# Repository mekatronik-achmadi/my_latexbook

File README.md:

# Install LaTeX

## Contents
- [ArchLinux](#archlinux)
	+ [TeXLive](#texlive)
	+ [TeXStudio](#texstudio)
	+ [Visual Studio Code](#visual-studio-code)
	+ [Makefile](#makefile)
- [Windows](#windows)
	+ [TeXLive](#texlive-1)
	+ [TeXStudio](#texstudio-1)

## ArchLinux

Example install command for ArchLinux, Manjaro, or any other Arch-based GNU/Linux distributions OS.

### TeXLive

To install TeXLive package, you can use command:

```sh
sudo pacman -S texlive-most texlive-bin latex2html latex2rtf dblatex minted biber pdftk
```

It will download approximately 800MB and installation size about 2.5GB.

This should be reproducible in other GNU/Linux distributions like Ubuntu or Fedora.

### TeXStudio

For editor, you can choose TeXStudio and can be installed using command:

```sh
sudo pacman -S texstudio
```

Installation size approximately 500MB (including Qt5 toolkit)

**NOTE:** If you use **minted**, you should use **-shell-escape**.
 
 Go to menu *Options* -> *Configure TexStudio* -> *Commands* to add **-shell-escape** like this:.

### Visual Studio Code

You can also use general code editor like Visual Studio Code to write LaTeX document.

First install VSCodium from this AUR package: https://aur.archlinux.org/packages/vscodium-bin/

Then install **LaTeX-Workshop** extension from *View* -> *Extension*.

### Makefile

You can also use this **Makefile** to build PDF from LaTeX documents

```make
TEXCC=pdflatex
BIBCC=bibtex
TEXFLAGS=-shell-escape -synctex=1 -interaction=nonstopmode
TEXFILE=$(shell basename --suffix=.tex $$(ls -1 *.tex))

# '-' sign mean keep going even if the command fail
all:
	-$(TEXCC) $(TEXFLAGS) $(TEXFILE).tex
	-$(BIBCC) $(TEXFILE).aux
	-$(TEXCC) $(TEXFLAGS) $(TEXFILE).tex
	-$(TEXCC) $(TEXFLAGS) $(TEXFILE).tex # run twice to update ToC/BibTeX

clean:
	rm -f *.out *.bbl *.blg *.lof *.lot *.nav *.vrb
	rm -f *.log *.toc *.synctex.gz  *.pyg *.snm
	rm -f *.aux *Notes.bib
	rm -f *.pdf
	rm -rf ./_minted*
```

Save as Makefile in same directory of any LaTeX documents, then run command:

```sh
make all
```

and to clean up you can run commmand:

```sh
make clean
```

## Windows

Example install process for Windows OS.

### TeXLive

Here step to Download TeXLive package:
- Open Mirror CTAN: https://ctan.org/mirrors.
- Choose closest mirror. Then choose **TeX Live**.
- Choose **Images**. Click to download the ISO file.

For example, Indonesian users can use this ISO file URL:

http://repo.ugm.ac.id/ctan/systems/texlive/Images/texlive2022-20220321.iso

**NOTE:** The ISO file approximately 5GB.

After download the ISO, first mount the ISO file (for example here as **E:** drive)

Then open **CMD** to run these commands:

```sh
> E:
> install-tl-windows.bat --location "E:/"
```

**NOTE:** Leave the CMD Window open during installations process

When GUI installer shown up, choose *Advanced*

Here there some recommended adjustments:
- Check *Adjust searchpath*.
- Choose *All* for *File associations*.
- Uncheck *Install TeXWorks* since TeXStudio will be used here.

Next go to *Selections* and click *Customize*.

In *Language* part, click *None* and then check only *US and UK English*

Then Click *Apply* and *OK*. The installation size should be reduced.

Last, click *Install* and wait until finished.

### TexStudio

You can download the Windows binary from Github release page:

https://github.com/texstudio-org/texstudio/releases/

**NOTE:** If you use **minted**, you should use **-shell-escape**.
 
 Go to menu *Options* -> *Configure TexStudio* -> *Commands* to add **-shell-escape** like this:.

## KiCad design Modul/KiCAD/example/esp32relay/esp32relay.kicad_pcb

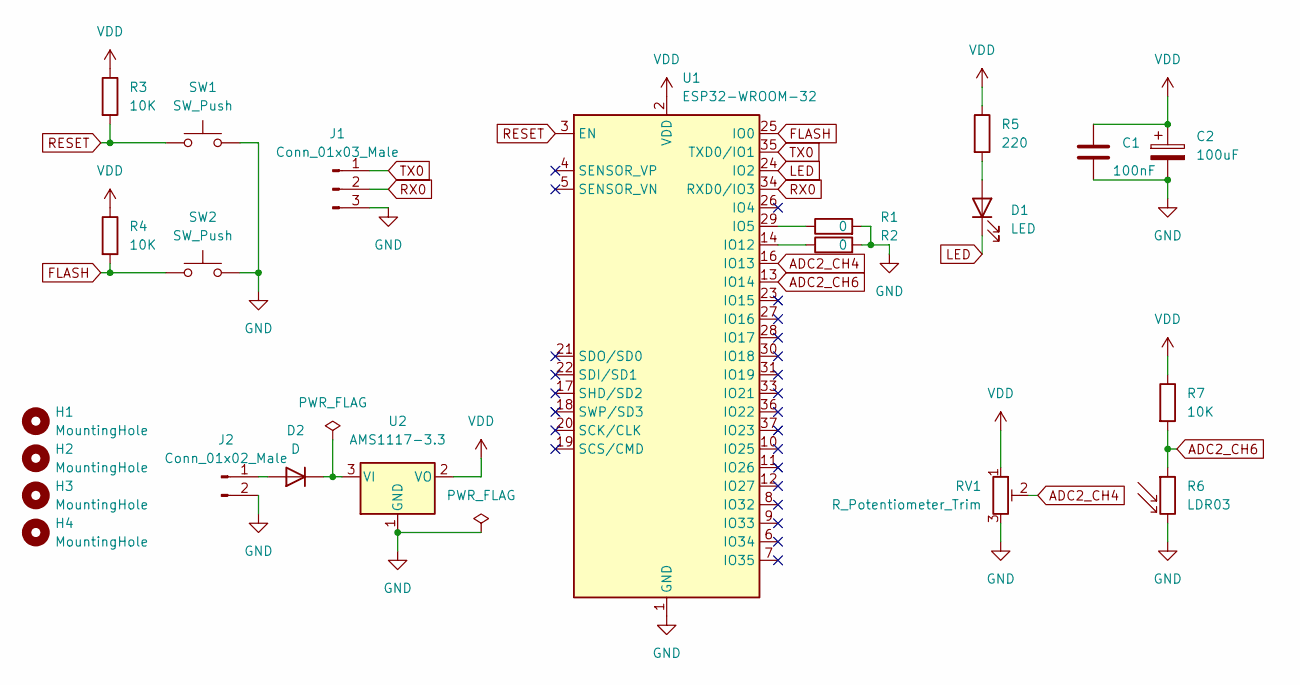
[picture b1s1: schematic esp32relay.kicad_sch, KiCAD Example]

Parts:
C1: 100nF; C_0805_2012Metric
C2: 100uF; C_0805_2012Metric
D1: LED; LED_0805_2012Metric
D2: D; D_SMA
H1, H2, H3, H4: MountingHole; MountingHole_2.5mm_Pad_Via
J1: Conn_01x03_Male; PinHeader_1x03_P2.54mm_Horizontal
J2: Conn_01x02_Male; Altech_AK300_1x02_P5.00mm_45-Degree
R1, R2: 0; R_0805_2012Metric
R3, R4, R7: 10K; R_0805_2012Metric
R5: 220; R_0805_2012Metric
R6: LDR03; R_LDR_10x8.5mm_P7.6mm_Vertical
RV1: R_Potentiometer_Trim; Potentiometer_Vishay_TS53YJ_Vertical
SW1, SW2: SW_Push; SW_PUSH_6mm
U1: ESP32-WROOM-32
U2: AMS1117-3.3; SOT-223-3_TabPin2

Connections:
ADC2_CH4: RV1.2, U1.16 (IO13)
ADC2_CH6: R6.1, R7.2, U1.13 (IO14)
FLASH: R4.2, SW2.1, U1.25 (IO0)
GND: C1.2, C2.2, J1.3, J2.2, R1.2, R2.2, R6.2, RV1.3, SW1.2, SW2.2, U1.1 (GND), U1.15 (GND), U1.38 (GND), U1.39 (GND), U2.1 (GND)
LED: D1.1 (K), U1.24 (IO2)
unnamed: D1.2 (A), R5.2
unnamed: D2.1 (K), U2.3 (VI)
unnamed: D2.2 (A), J2.1
unnamed: R1.1, U1.29 (IO5)
unnamed: R2.1, U1.14 (IO12)
RESET: R3.2, SW1.1, U1.3 (EN)
RX0: J1.2, U1.34 (RXD0/IO3)
TX0: J1.1, U1.35 (TXD0/IO1)
VDD: C1.1, C2.1, R3.1, R4.1, R5.1, R7.1, RV1.1, U1.2 (VDD), U2.2 (VO)

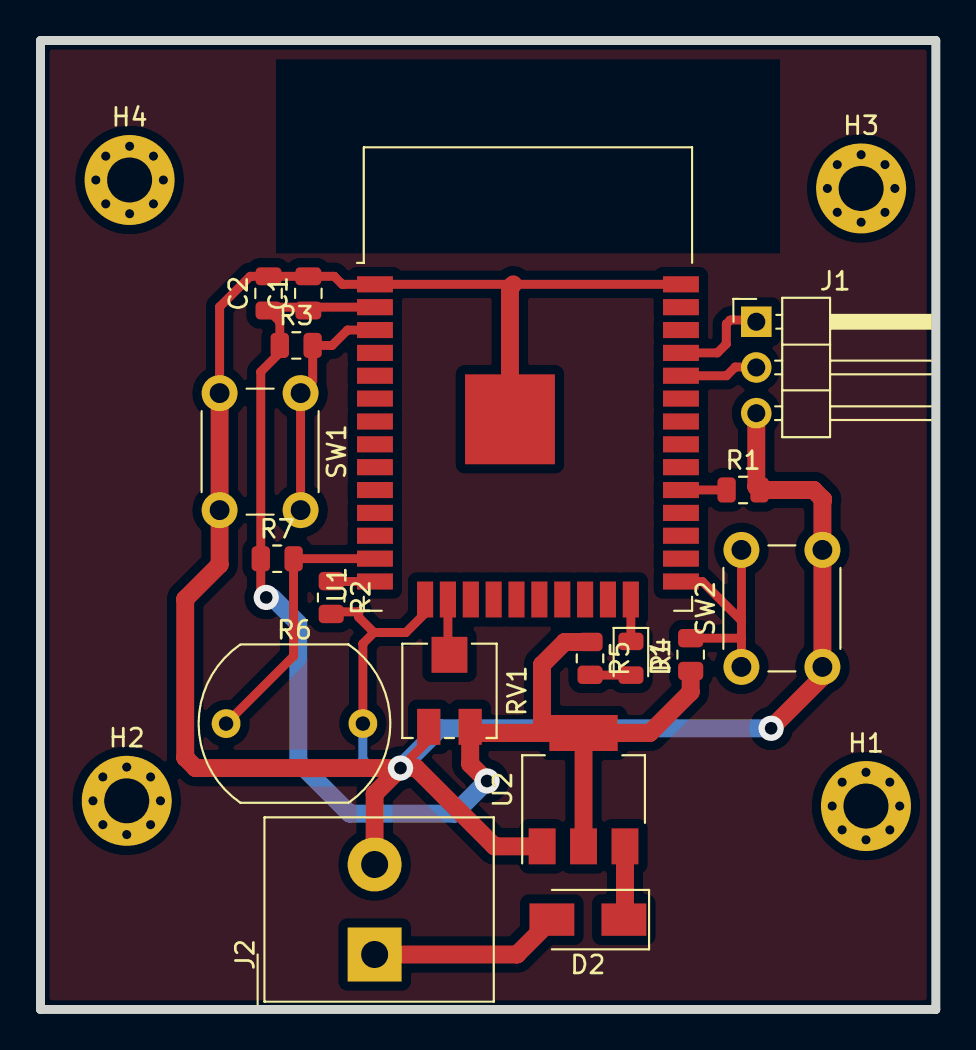
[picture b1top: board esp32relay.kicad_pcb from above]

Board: 2 copper layers, 49.7 x 53.8 mm, 22 parts (0 on the bottom side), 14 nets.

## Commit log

2018-04-18 buku Thesis
2018-04-19 finish table of Content format
2018-04-19 progres buku
2018-04-20 progress
2018-04-20 progres
2018-04-20 reset image numbering
2018-04-21 Progrees
2018-04-21 Progres I
2018-05-15 git collaborative
2018-05-16 Git LaTeX book
2018-05-16 Git Kolaborasi
2018-05-21 Git sources
2018-05-22 test python
2018-06-19 extended paper
2018-06-20 haduh
2018-07-03 Progres 2
2018-08-13 hopes no problem
2018-11-24 modul
2018-11-24 dokumen
2018-11-25 bab 1 80%
2018-11-25 Modul Linux Bab 1 85%
2018-11-25 bab 1 fix
2018-11-26 bab 1 lengkap
2018-11-26 Mulai bab 2
2018-11-27 bab 2
2018-11-28 bab 2 oke
2019-02-20 last progress
2019-03-21 no error
2019-03-24 modul pelatihan AVR
2019-03-25 AVR Module: C
2019-03-25 AVR Modul:C
2019-03-25 clean up
2019-03-25 modul AVR: C
2019-03-27 update modul AVR: C
2019-03-27 Modul AVR: Simulation
2019-03-31 register operation
2019-04-08 modul pengantar selesai
2019-05-01 clean pdf too
2019-05-01 no pdf
2019-05-13 H to HT
2019-05-13 no space nor tab after end_minted
2019-09-02 reworking
2019-09-05 laporan pikoakustik
2019-09-05 piko diagram
2019-09-05 stm32 ppt
2019-09-05 stm32 training
2019-09-06 stm32bluepill training
2019-09-06 stm32 training polling
2019-09-07 actual image
2019-09-08 laporan teknis piko
2019-10-09 fix AVR
2020-01-14 preliminary report
2020-02-15 new report
2020-02-15 laporan
2020-02-24 pikoakustik ITB docs
2021-07-19 Yugioh Duel Links notes
2021-07-25 Update Duel Links notes
2021-07-29 update Duel Links note
2021-10-01 Duel Links Notes
2021-10-11 initial modul
2021-10-11 buku Matlab
2021-10-11 pembelajaran MATLAB
2021-10-12 matlab module
2021-10-12 update module
2021-10-12 Matlab Bab 1 selesai
2021-10-13 matlab
2021-10-13 modul matlab
2021-10-13 progres matlab
2021-10-14 progress MATLAB
2021-10-14 tutorial MATLAB
2021-10-16 matlab fungsi
2021-10-16 update cover
2021-10-16 matlab plot ok
2021-10-16 Matlab tinggal Git-SCM
2021-10-16 Matlab Git
2021-10-16 finish for now
2021-10-17 Git-CLI only
2021-10-17 Git-SCM temporary finished
2021-10-18 materi dipisah
2021-10-19 matlab 2nd day
2021-10-23 YuGiOh Duel-Links
2021-10-23 examples
2021-10-24 display OK
2021-10-24 I2C membingungkan
2021-10-24 I2C error 255
2021-10-24 I2C are trash
2021-10-25 f4 disc variant
2021-10-25 f4 working
2021-10-25 hardware source ok
2021-10-25 demo ok
2021-10-29 some update
2021-11-19 f4disc adc
2021-12-15 sourcecodes move to examples
2022-04-13 Yugioh Duel Links
2022-04-30 latex tutorial
2022-05-06 tutorial latex
2022-05-06 latex tutorial semidone
2022-05-09 latex studio
2022-05-10 latex tutorial JASA
2022-10-04 Update YuGiOh Duel Links notes
2022-10-06 Update Materi Matlab
2022-10-06 Update Matlab Hardware
2022-10-06 Matlab ESP32
2022-10-06 Start Serial Matlab
2022-10-07 Matlab to ESP32
2022-10-07 Matlab Hardware Done
2022-12-09 Start KiCAD Tutorial
2022-12-09 Progress Tutorial KiCAD
2022-12-09 KiCAD
2022-12-09 KiCAD tutorial combine Windows-10 and ArchLinux
2022-12-10 Progress KiCAD
2022-12-10 KiCAD Install Guide
2022-12-11 KiCAD Workflow
2022-12-11 KiCAD contoh komponen
2022-12-11 KiCAD dasar konsep
2022-12-11 KiCAD Sch
2022-12-11 Menu Keys
2022-12-11 MenuKeys
2022-12-12 KiCAD Footprint Assigment
2022-12-12 KiCAD PCB start
2022-12-14 KiCAD PCB
2022-12-14 KiCAD Fab Files
2022-12-14 KiCAD Fabrication
2022-12-14 KiCAD Tutorial
2022-12-14 KiCAD Revision
2022-12-21 Some Clean-Up and Makefile additions
2022-12-21 CleanUp some whitespace
2022-12-21 Drop AchmadiOS (unmaintained)
2022-12-21 Add Readme
2022-12-21 Readme
2022-12-21 Readme install Latex
2022-12-25 Drop Linux (unmaintained)
2023-01-10 Update KiCAD Gerber Tips
2023-01-10 Gerber Viewer
2023-01-16 PCB Manufacturers
2023-01-27 KiCAD PDF
2023-02-02 Yugioh Duel Links note update
2023-02-03 Yugioh Duel Links Note
2023-05-02 Update Yugioh Duel Link Notes
2023-10-01 Stop Duel Links for a while
2023-11-09 Remove Unnecessary
2023-11-19 Tutorial DevChip
2023-11-20 Tutorial
2023-11-20 Tutorial ChipDev
2023-11-20 KiCAD Git
2023-11-20 ESP32 Windows
2023-11-20 ChipDev Book
2023-11-20 Editor
